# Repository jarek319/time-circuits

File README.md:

# time-circuits
A Wifi-enabled clock inspired by the Time Circuits prop from the Back to the Future movies

The hardest part about this project was deciding what to display for Past and Future...

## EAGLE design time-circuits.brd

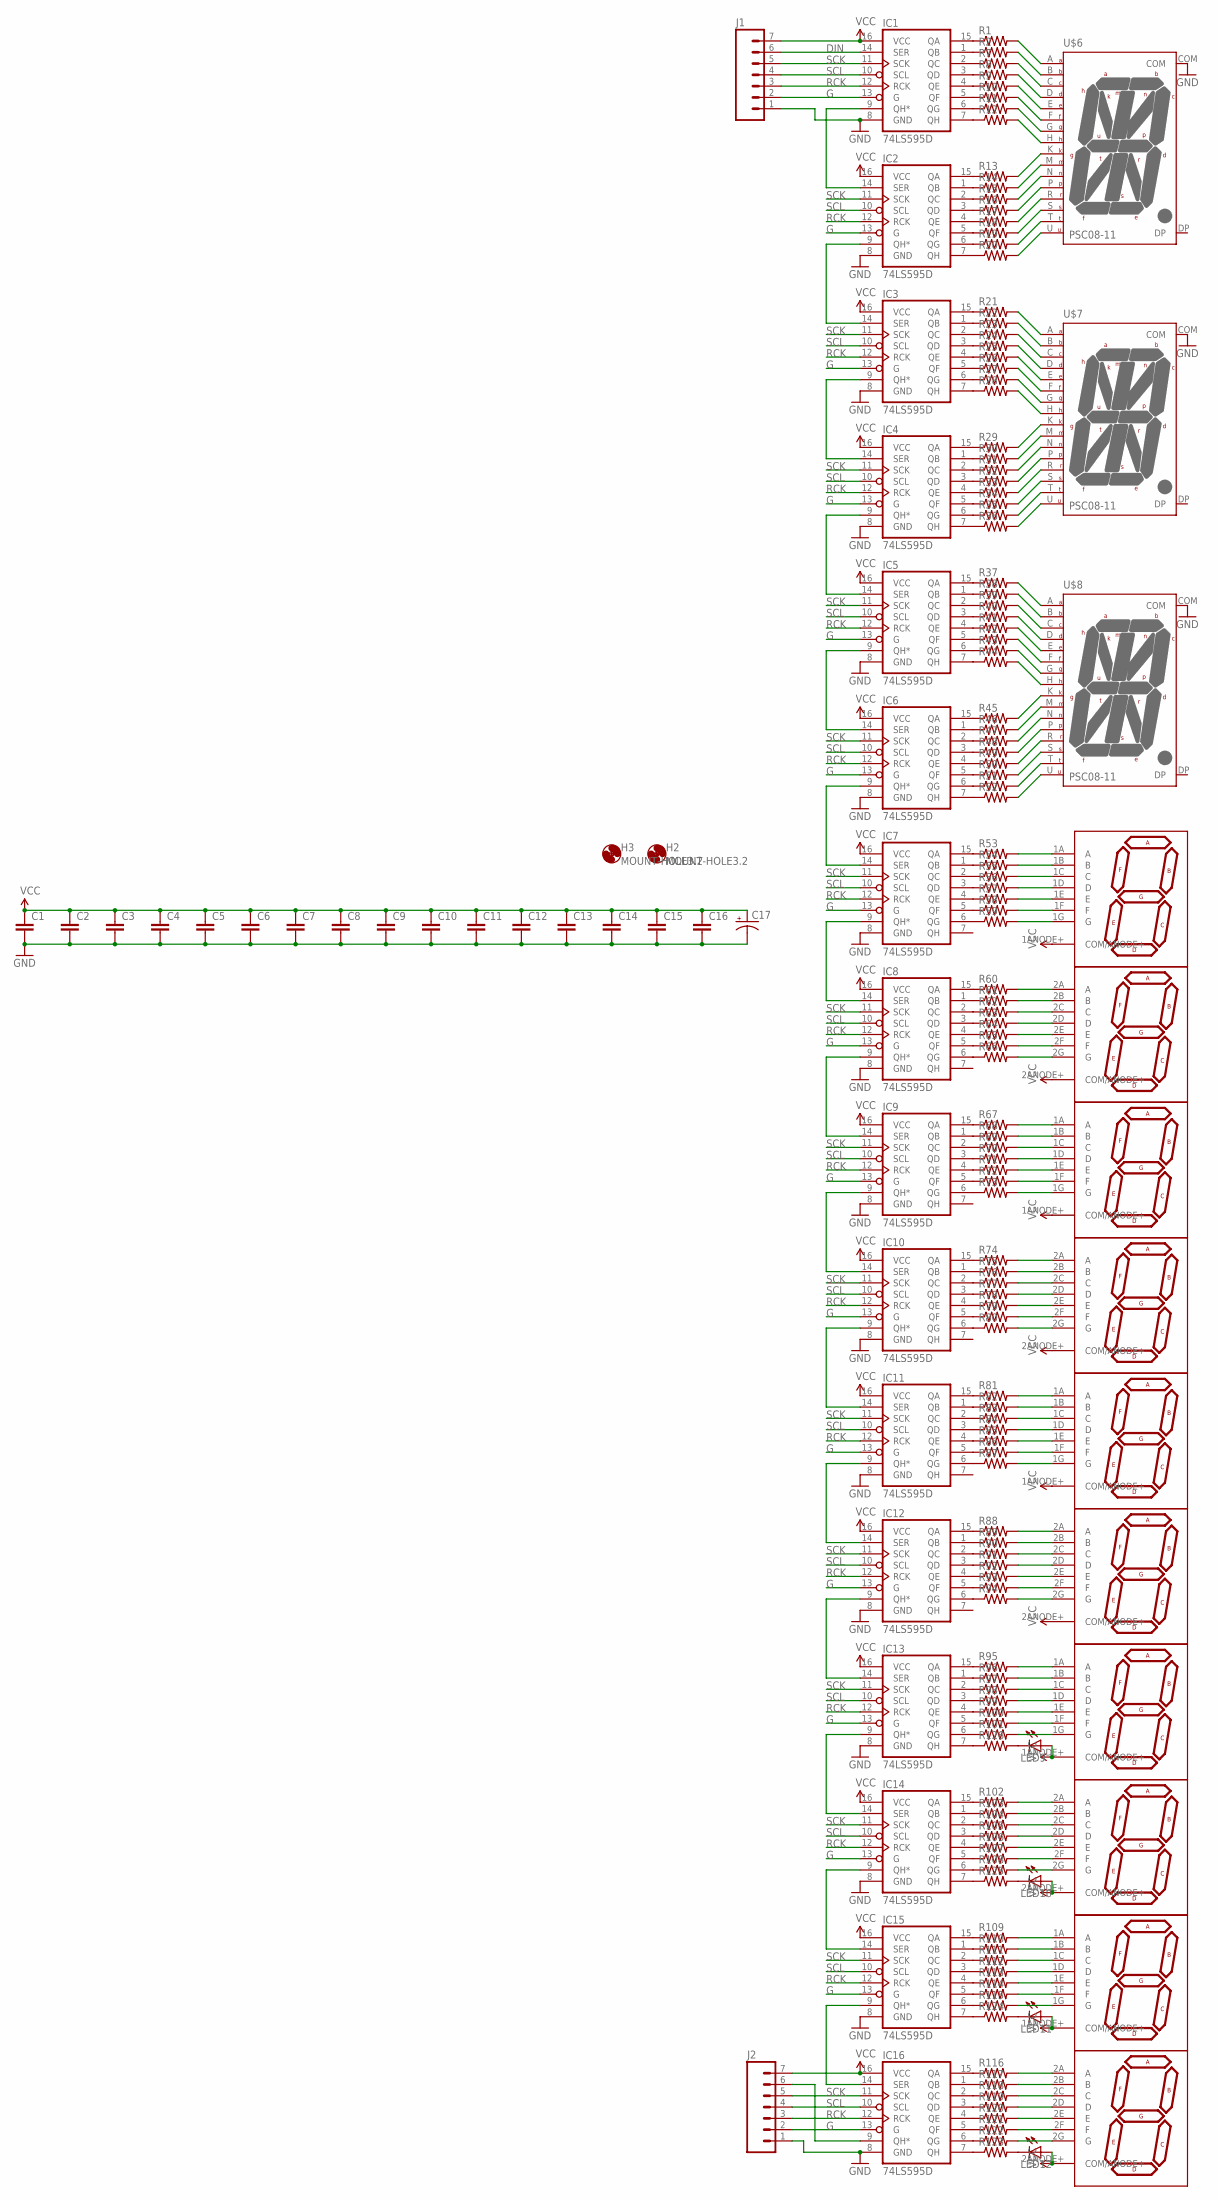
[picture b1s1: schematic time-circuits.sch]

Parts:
C1, C2, C3, C4, C5, C6, C7, C8, C9, C10, C11, C12, C13, C14, C15, C16: CAP0805; 0805
C17: CAP_POLH13; PANASONIC_H13
H2, H3: MOUNT-HOLE3.2; 3,2
IC1, IC2, IC3, IC4, IC5, IC6, IC7, IC8, IC9, IC10, IC11, IC12, IC13, IC14, IC15, IC16: 74LS595D; SO16
J1, J2: M07LOCK; 1X07_LOCK
LED9, LED10, LED11, LED12: LED5MM
R1, R2, R7, R8, R9, R10, R11, R12, R13, R14, R15, R16, R17, R18, R19, R20, R21, R22, R23, R24, R25, R26, R27, R28, R29, R30, R31, R32, R33, R34, R35, R36, R37, R38, R39, R40, R41, R42, R43, R44, R45, R46, R47, R48, R49, R50, R51, R52, R53, R54, R55, R56, R57, R58, R59, R60, R61, R62, R63, R64, R65, R66, R67, R68, R69, R70, R71, R72, R73, R74, R75, R76, R77, R78, R79, R80, R81, R82, R83, R84, R85, R86, R87, R88, R89, R90, R91, R92, R93, R94, R95, R96, R97, R98, R99, R100, R101, R102, R103, R104, R105, R106, R107, R108, R109, R110, R111, R112, R113, R114, R115, R116, R117, R118, R119, R120, R121, R122, R123, R124, R125, R126: RESISTOR0805-RES; 0805
U$1, U$2, U$3, U$4, U$5: DA08-11
U$6, U$7, U$8: PSC08-11

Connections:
DIN: IC1.14 (SER), J1.6
G: IC1.13 (G), IC2.13 (G), IC3.13 (G), IC4.13 (G), IC5.13 (G), IC6.13 (G), IC7.13 (G), IC8.13 (G), IC9.13 (G), IC10.13 (G), IC11.13 (G), IC12.13 (G), IC13.13 (G), IC14.13 (G), IC15.13 (G), IC16.13 (G), J1.2, J2.2
GND: C1.2, C2.2, C3.2, C4.2, C5.2, C6.2, C7.2, C8.2, C9.2, C10.2, C11.2, C12.2, C13.2, C14.2, C15.2, C16.2, C17.-, IC1.8 (GND), IC2.8 (GND), IC3.8 (GND), IC4.8 (GND), IC5.8 (GND), IC6.8 (GND), IC7.8 (GND), IC8.8 (GND), IC9.8 (GND), IC10.8 (GND), IC11.8 (GND), IC12.8 (GND), IC13.8 (GND), IC14.8 (GND), IC15.8 (GND), IC16.8 (GND), J1.1, J2.1, U$6.COM, U$7.COM, U$8.COM
unnamed: IC5.9 (QH*), IC6.14 (SER)
unnamed: IC1.9 (QH*), IC2.14 (SER)
unnamed: IC1.15 (QA), R1.1
unnamed: IC1.1 (QB), R2.1
unnamed: IC1.2 (QC), R7.1
unnamed: IC1.3 (QD), R8.1
unnamed: IC1.4 (QE), R9.1
unnamed: IC1.5 (QF), R10.1
unnamed: IC1.6 (QG), R11.1
unnamed: IC1.7 (QH), R12.1
unnamed: IC2.15 (QA), R13.1
unnamed: IC2.1 (QB), R14.1
unnamed: IC2.2 (QC), R15.1
unnamed: R53.2, U$1.1A (A)
unnamed: IC16.9 (QH*), J2.6
unnamed: R54.2, U$1.1B (B)
unnamed: R55.2, U$1.1C (C)
unnamed: IC2.3 (QD), R16.1
unnamed: IC2.4 (QE), R17.1
unnamed: R56.2, U$1.1D (D)
unnamed: R57.2, U$1.1E (E)
unnamed: R58.2, U$1.1F (F)
unnamed: R59.2, U$1.1G (G)
unnamed: R60.2, U$1.2A (A)
unnamed: R61.2, U$1.2B (B)
unnamed: R62.2, U$1.2C (C)
unnamed: IC2.5 (QF), R18.1
unnamed: IC2.6 (QG), R19.1
unnamed: IC2.7 (QH), R20.1
unnamed: R1.2, U$6.A
unnamed: R2.2, U$6.B
unnamed: R7.2, U$6.C
unnamed: R8.2, U$6.D
unnamed: R9.2, U$6.E
unnamed: R10.2, U$6.F
unnamed: R11.2, U$6.G
unnamed: R12.2, U$6.H
unnamed: R13.2, U$6.K
unnamed: R14.2, U$6.M
unnamed: R15.2, U$6.N
unnamed: R16.2, U$6.P
unnamed: R17.2, U$6.R
unnamed: R18.2, U$6.S
unnamed: R19.2, U$6.T
unnamed: R20.2, U$6.U
unnamed: IC3.9 (QH*), IC4.14 (SER)
unnamed: IC3.15 (QA), R21.1
unnamed: IC3.1 (QB), R22.1
unnamed: IC3.2 (QC), R23.1
unnamed: IC3.3 (QD), R24.1
unnamed: IC3.4 (QE), R25.1
unnamed: IC3.5 (QF), R26.1
unnamed: IC3.6 (QG), R27.1
unnamed: IC3.7 (QH), R28.1
unnamed: IC4.15 (QA), R29.1
unnamed: IC4.1 (QB), R30.1
unnamed: IC4.2 (QC), R31.1
unnamed: IC4.3 (QD), R32.1
unnamed: IC4.4 (QE), R33.1
unnamed: IC4.5 (QF), R34.1
unnamed: IC4.6 (QG), R35.1
unnamed: IC4.7 (QH), R36.1
unnamed: R21.2, U$7.A
unnamed: R22.2, U$7.B
unnamed: R23.2, U$7.C
unnamed: R24.2, U$7.D
unnamed: R25.2, U$7.E
unnamed: R26.2, U$7.F
unnamed: R27.2, U$7.G
unnamed: R28.2, U$7.H
unnamed: R29.2, U$7.K
unnamed: R30.2, U$7.M
unnamed: R31.2, U$7.N
unnamed: R32.2, U$7.P
unnamed: R33.2, U$7.R
unnamed: R34.2, U$7.S
unnamed: R35.2, U$7.T
unnamed: R36.2, U$7.U
unnamed: IC5.15 (QA), R37.1
unnamed: IC5.1 (QB), R38.1
unnamed: IC5.2 (QC), R39.1
unnamed: IC5.3 (QD), R40.1
unnamed: IC5.4 (QE), R41.1
unnamed: IC5.5 (QF), R42.1
unnamed: IC5.6 (QG), R43.1
unnamed: IC5.7 (QH), R44.1
unnamed: IC6.15 (QA), R45.1
unnamed: IC6.1 (QB), R46.1
unnamed: IC6.2 (QC), R47.1
unnamed: IC6.3 (QD), R48.1
unnamed: IC6.4 (QE), R49.1
unnamed: IC6.5 (QF), R50.1
unnamed: IC6.6 (QG), R51.1
unnamed: IC6.7 (QH), R52.1
unnamed: R37.2, U$8.A
unnamed: R38.2, U$8.B
unnamed: R39.2, U$8.C
unnamed: R40.2, U$8.D
unnamed: R41.2, U$8.E
unnamed: R42.2, U$8.F
unnamed: R43.2, U$8.G
unnamed: R44.2, U$8.H
unnamed: R45.2, U$8.K
unnamed: R46.2, U$8.M
unnamed: R47.2, U$8.N
unnamed: R48.2, U$8.P
unnamed: R49.2, U$8.R
unnamed: R50.2, U$8.S
unnamed: R51.2, U$8.T
unnamed: R52.2, U$8.U
unnamed: IC2.9 (QH*), IC3.14 (SER)
unnamed: IC4.9 (QH*), IC5.14 (SER)
unnamed: IC6.9 (QH*), IC7.14 (SER)
unnamed: IC7.15 (QA), R53.1
unnamed: IC7.1 (QB), R54.1
unnamed: IC7.2 (QC), R55.1
unnamed: IC7.3 (QD), R56.1
unnamed: IC7.4 (QE), R57.1
unnamed: IC7.5 (QF), R58.1
unnamed: IC7.6 (QG), R59.1
unnamed: IC7.9 (QH*), IC8.14 (SER)
unnamed: IC8.15 (QA), R60.1
unnamed: IC8.1 (QB), R61.1
unnamed: IC8.2 (QC), R62.1
unnamed: IC8.3 (QD), R63.1
unnamed: IC8.4 (QE), R64.1
unnamed: IC8.5 (QF), R65.1
unnamed: IC8.6 (QG), R66.1
unnamed: R63.2, U$1.2D (D)
unnamed: R64.2, U$1.2E (E)
unnamed: R65.2, U$1.2F (F)
unnamed: R66.2, U$1.2G (G)
unnamed: R67.2, U$2.1A (A)
unnamed: R68.2, U$2.1B (B)
unnamed: R69.2, U$2.1C (C)
unnamed: R70.2, U$2.1D (D)
unnamed: R71.2, U$2.1E (E)
unnamed: R72.2, U$2.1F (F)
unnamed: R73.2, U$2.1G (G)
unnamed: R74.2, U$2.2A (A)
unnamed: R75.2, U$2.2B (B)
unnamed: R76.2, U$2.2C (C)
unnamed: IC8.9 (QH*), IC9.14 (SER)
unnamed: IC9.15 (QA), R67.1
unnamed: IC9.1 (QB), R68.1
unnamed: IC9.2 (QC), R69.1
unnamed: IC9.3 (QD), R70.1
unnamed: IC9.4 (QE), R71.1
unnamed: IC9.5 (QF), R72.1
unnamed: IC9.6 (QG), R73.1
unnamed: R77.2, U$2.2D (D)
unnamed: R78.2, U$2.2E (E)
unnamed: R79.2, U$2.2F (F)
unnamed: R80.2, U$2.2G (G)
unnamed: R81.2, U$3.1A (A)
unnamed: R82.2, U$3.1B (B)
unnamed: R83.2, U$3.1C (C)
unnamed: IC9.9 (QH*), IC10.14 (SER)
unnamed: IC10.15 (QA), R74.1
unnamed: IC10.1 (QB), R75.1
unnamed: IC10.2 (QC), R76.1
unnamed: IC10.3 (QD), R77.1
unnamed: IC10.4 (QE), R78.1
unnamed: IC10.5 (QF), R79.1
unnamed: IC10.6 (QG), R80.1
unnamed: R84.2, U$3.1D (D)
unnamed: R85.2, U$3.1E (E)
unnamed: R86.2, U$3.1F (F)
unnamed: R87.2, U$3.1G (G)
unnamed: R88.2, U$3.2A (A)
unnamed: R89.2, U$3.2B (B)
unnamed: R90.2, U$3.2C (C)
unnamed: IC10.9 (QH*), IC11.14 (SER)
unnamed: IC11.15 (QA), R81.1
unnamed: IC11.1 (QB), R82.1
unnamed: IC11.2 (QC), R83.1
unnamed: IC11.3 (QD), R84.1
unnamed: IC11.4 (QE), R85.1
unnamed: IC11.5 (QF), R86.1
unnamed: IC11.6 (QG), R87.1
unnamed: R91.2, U$3.2D (D)
unnamed: R92.2, U$3.2E (E)
unnamed: R93.2, U$3.2F (F)
unnamed: R94.2, U$3.2G (G)
unnamed: R95.2, U$4.1A (A)
unnamed: R96.2, U$4.1B (B)
unnamed: R97.2, U$4.1C (C)
unnamed: IC11.9 (QH*), IC12.14 (SER)
unnamed: IC12.15 (QA), R88.1
unnamed: IC12.1 (QB), R89.1
unnamed: IC12.2 (QC), R90.1
unnamed: IC12.3 (QD), R91.1
unnamed: IC12.4 (QE), R92.1
unnamed: IC12.5 (QF), R93.1
unnamed: IC12.6 (QG), R94.1
unnamed: R98.2, U$4.1D (D)
unnamed: R99.2, U$4.1E (E)
unnamed: R100.2, U$4.1F (F)
unnamed: R101.2, U$4.1G (G)
unnamed: R102.2, U$4.2A (A)
unnamed: R103.2, U$4.2B (B)
unnamed: R104.2, U$4.2C (C)
unnamed: IC12.9 (QH*), IC13.14 (SER)
unnamed: IC13.15 (QA), R95.1
unnamed: IC13.1 (QB), R96.1
unnamed: IC13.2 (QC), R97.1
unnamed: IC13.3 (QD), R98.1
unnamed: IC13.4 (QE), R99.1
unnamed: IC13.5 (QF), R100.1
unnamed: IC13.6 (QG), R101.1
unnamed: IC13.9 (QH*), IC14.14 (SER)
unnamed: IC14.15 (QA), R102.1
unnamed: IC14.1 (QB), R103.1
unnamed: IC14.2 (QC), R104.1
unnamed: IC14.3 (QD), R105.1
unnamed: IC14.4 (QE), R106.1
unnamed: IC14.5 (QF), R107.1
unnamed: IC14.6 (QG), R108.1
unnamed: IC14.9 (QH*), IC15.14 (SER)
unnamed: IC15.15 (QA), R109.1
unnamed: IC15.1 (QB), R110.1
unnamed: IC15.2 (QC), R111.1
unnamed: IC15.3 (QD), R112.1
unnamed: IC15.4 (QE), R113.1
unnamed: IC15.5 (QF), R114.1
unnamed: IC15.6 (QG), R115.1
unnamed: IC15.9 (QH*), IC16.14 (SER)
unnamed: IC16.15 (QA), R116.1
unnamed: IC16.1 (QB), R117.1
unnamed: IC16.2 (QC), R118.1
unnamed: IC16.3 (QD), R119.1
unnamed: IC16.4 (QE), R120.1
unnamed: IC16.5 (QF), R121.1
unnamed: IC16.6 (QG), R122.1
unnamed: R105.2, U$4.2D (D)
unnamed: R106.2, U$4.2E (E)
unnamed: R107.2, U$4.2F (F)
unnamed: R108.2, U$4.2G (G)
unnamed: R109.2, U$5.1A (A)
unnamed: R110.2, U$5.1B (B)
unnamed: R111.2, U$5.1C (C)
unnamed: R112.2, U$5.1D (D)
unnamed: R113.2, U$5.1E (E)
unnamed: R114.2, U$5.1F (F)
unnamed: R115.2, U$5.1G (G)
unnamed: R116.2, U$5.2A (A)
unnamed: R117.2, U$5.2B (B)
unnamed: R118.2, U$5.2C (C)
unnamed: R119.2, U$5.2D (D)
unnamed: R120.2, U$5.2E (E)
unnamed: R121.2, U$5.2F (F)
unnamed: R122.2, U$5.2G (G)
unnamed: IC16.7 (QH), R123.1
unnamed: IC15.7 (QH), R124.1
unnamed: IC14.7 (QH), R125.1
unnamed: IC13.7 (QH), R126.1
unnamed: LED9.K (C), R126.2
unnamed: LED10.K (C), R125.2
unnamed: LED11.K (C), R124.2
unnamed: LED12.K (C), R123.2
RCK: IC1.12 (RCK), IC2.12 (RCK), IC3.12 (RCK), IC4.12 (RCK), IC5.12 (RCK), IC6.12 (RCK), IC7.12 (RCK), IC8.12 (RCK), IC9.12 (RCK), IC10.12 (RCK), IC11.12 (RCK), IC12.12 (RCK), IC13.12 (RCK), IC14.12 (RCK), IC15.12 (RCK), IC16.12 (RCK), J1.3, J2.3
SCK: IC1.11 (SCK), IC2.11 (SCK), IC3.11 (SCK), IC4.11 (SCK), IC5.11 (SCK), IC6.11 (SCK), IC7.11 (SCK), IC8.11 (SCK), IC9.11 (SCK), IC10.11 (SCK), IC11.11 (SCK), IC12.11 (SCK), IC13.11 (SCK), IC14.11 (SCK), IC15.11 (SCK), IC16.11 (SCK), J1.5, J2.5
SCL: IC1.10 (SCL), IC2.10 (SCL), IC3.10 (SCL), IC4.10 (SCL), IC5.10 (SCL), IC6.10 (SCL), IC7.10 (SCL), IC8.10 (SCL), IC9.10 (SCL), IC10.10 (SCL), IC11.10 (SCL), IC12.10 (SCL), IC13.10 (SCL), IC14.10 (SCL), IC15.10 (SCL), IC16.10 (SCL), J1.4, J2.4
VCC: C1.1, C2.1, C3.1, C4.1, C5.1, C6.1, C7.1, C8.1, C9.1, C10.1, C11.1, C12.1, C13.1, C14.1, C15.1, C16.1, C17.+, IC1.16 (VCC), IC2.16 (VCC), IC3.16 (VCC), IC4.16 (VCC), IC5.16 (VCC), IC6.16 (VCC), IC7.16 (VCC), IC8.16 (VCC), IC9.16 (VCC), IC10.16 (VCC), IC11.16 (VCC), IC12.16 (VCC), IC13.16 (VCC), IC14.16 (VCC), IC15.16 (VCC), IC16.16 (VCC), J1.7, J2.7, LED9.A, LED10.A, LED11.A, LED12.A, U$1.1ANODE+ (COM/ANODE+), U$1.2ANODE+ (COM/ANODE+), U$2.1ANODE+ (COM/ANODE+), U$2.2ANODE+ (COM/ANODE+), U$3.1ANODE+ (COM/ANODE+), U$3.2ANODE+ (COM/ANODE+), U$4.1ANODE+ (COM/ANODE+), U$4.2ANODE+ (COM/ANODE+), U$5.1ANODE+ (COM/ANODE+), U$5.2ANODE+ (COM/ANODE+)

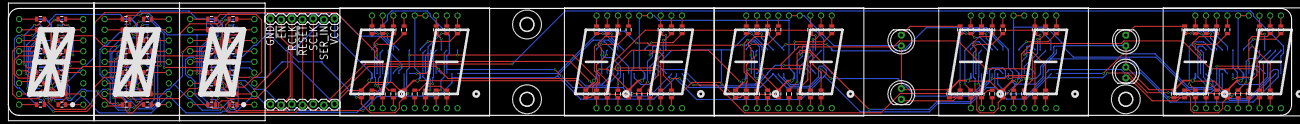
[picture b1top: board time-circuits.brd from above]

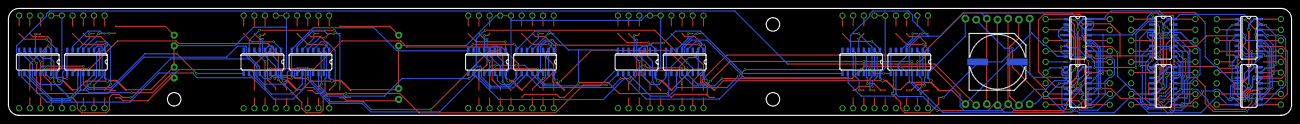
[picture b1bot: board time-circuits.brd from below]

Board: 2 copper layers, 304.8 x 25.4 mm, 172 parts (17 on the bottom side), 267 nets.

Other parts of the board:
H1: MOUNT-HOLE3.2; 3,2

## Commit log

2018-07-05 design tested: working

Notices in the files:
parts and their libraries:
SparkFun-Resistors: Licensing: CC v3.0 Share-Alike You are welcome to use this library for commercial purposes.
SparkFun-DigitalIC: Licensing: Creative Commons ShareAlike 4.0 International - https://creativecommons.org/licenses/by-sa/4.0
